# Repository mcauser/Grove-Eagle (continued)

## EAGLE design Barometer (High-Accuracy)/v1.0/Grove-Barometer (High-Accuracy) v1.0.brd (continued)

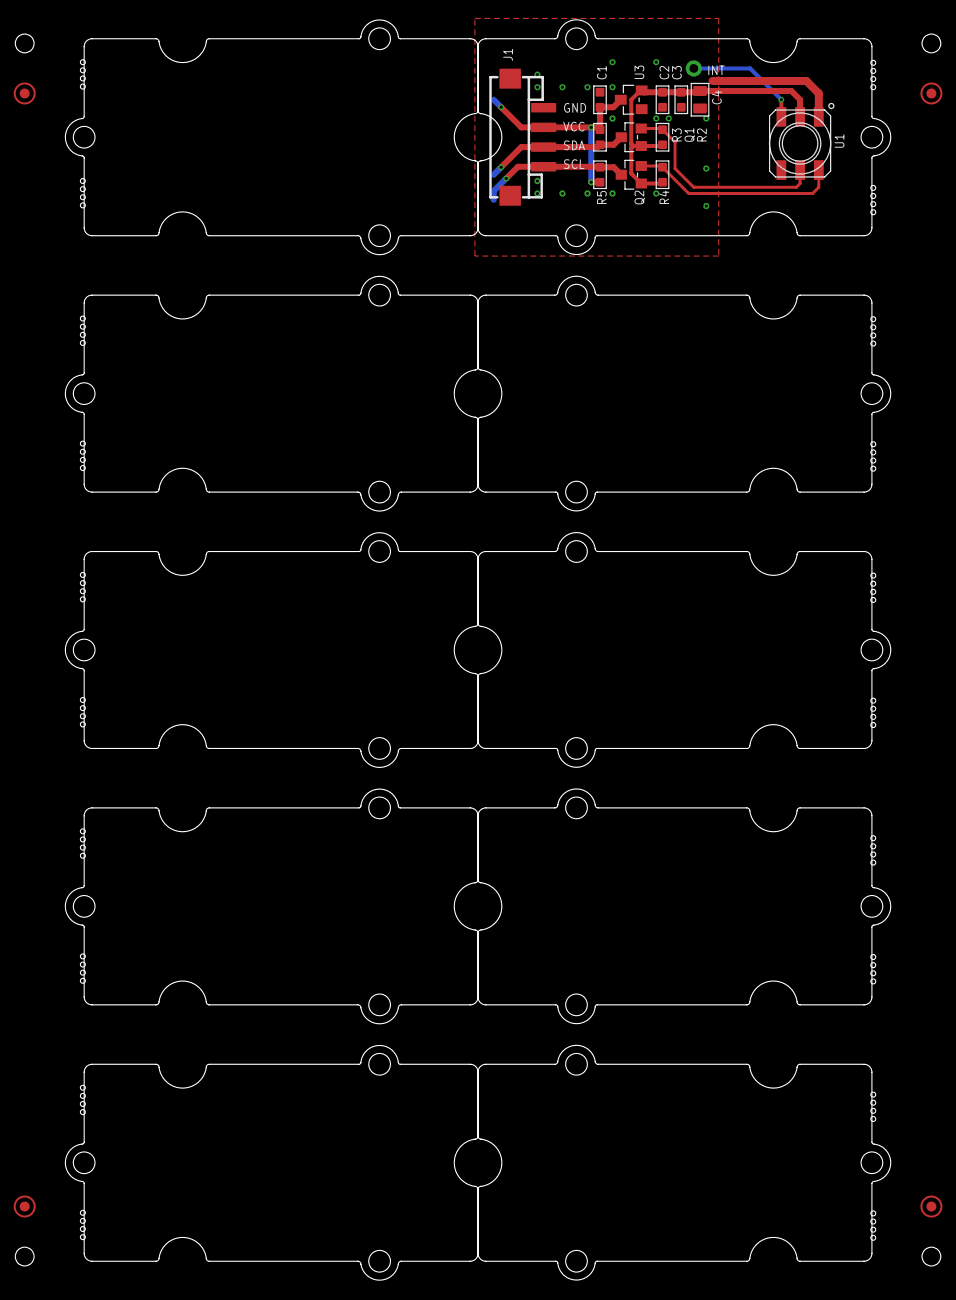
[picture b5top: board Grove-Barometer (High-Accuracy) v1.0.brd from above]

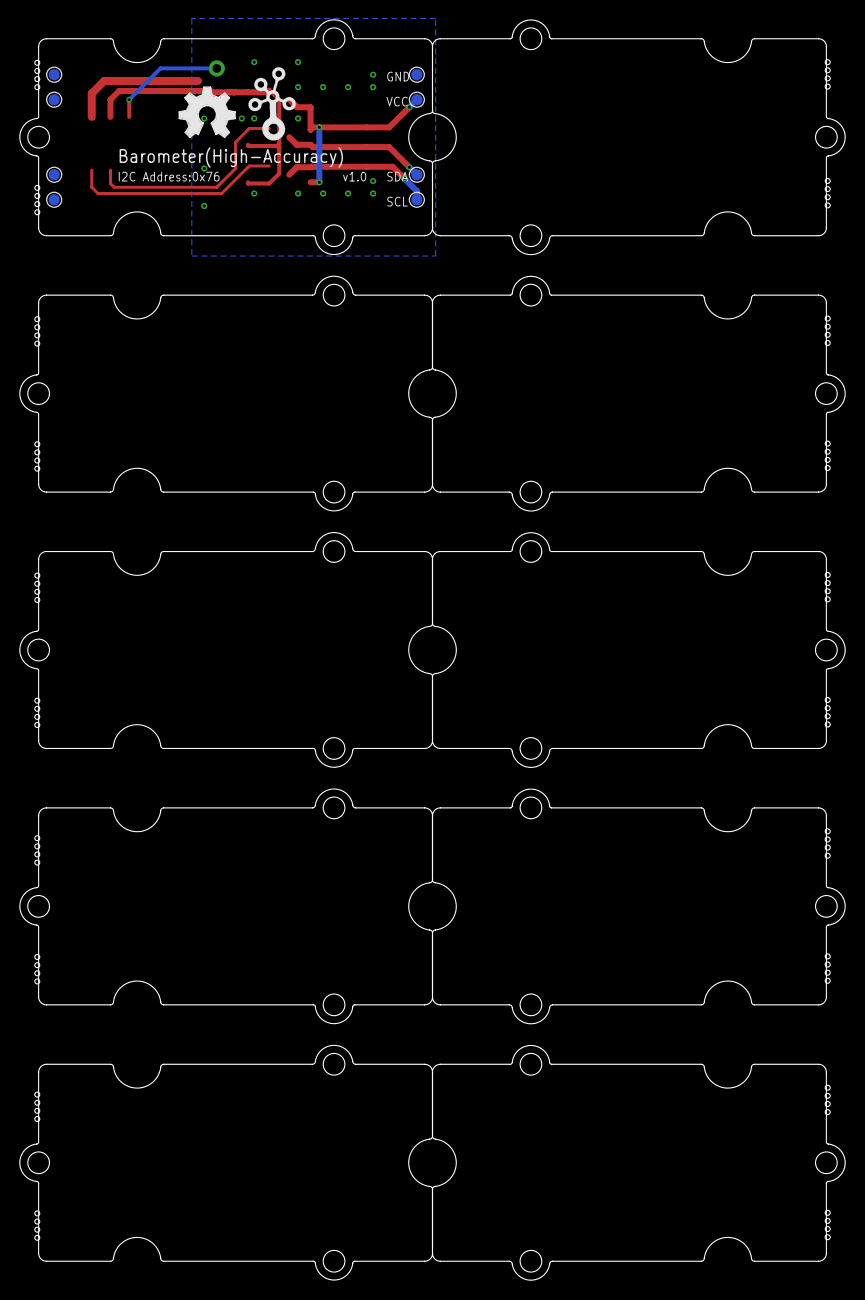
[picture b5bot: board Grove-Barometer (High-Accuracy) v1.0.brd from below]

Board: 2 copper layers, 83.8 x 128.0 mm, 38 parts (10 on the bottom side), 8 nets.

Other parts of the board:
U$4, U$5, U$8, U$9, U$10, U$11, U$12, U$13, U$14, U$15: GROVE-2CONNECTOR-SMD
U$6: OSHW_FILLX200_NOTEXT
U$7: TWIGLOGO

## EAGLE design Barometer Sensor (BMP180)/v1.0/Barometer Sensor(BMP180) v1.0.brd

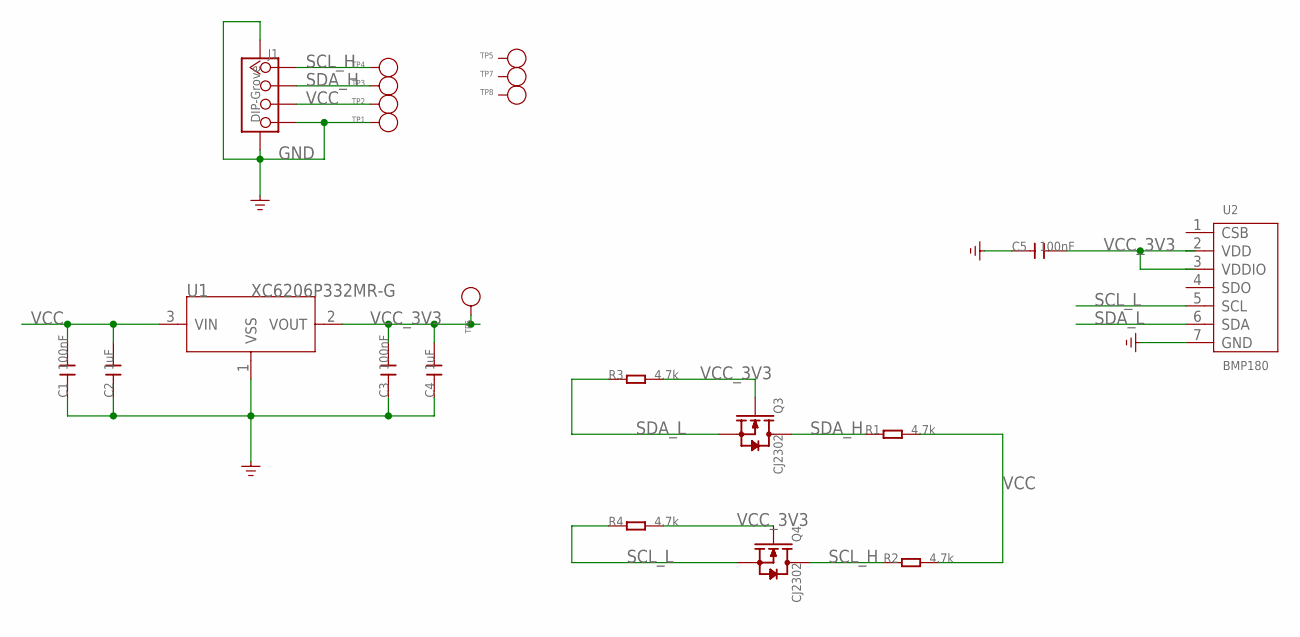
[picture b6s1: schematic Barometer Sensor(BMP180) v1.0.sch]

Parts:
C1, C3, C5: 100nF; C0603
C2, C4: 1uF; C0603
J1: DIP-Grove; 4P-SMD-2.0
Q3, Q4: CJ2302; SOT23
R1, R2, R3, R4: 4.7k; R0603
TP1, TP2, TP3, TP4, TP5, TP6, TP7, TP8: PAD-TEST-POINT'4545'; TP_4545
U1: XC6206P332MR-G; SOT23
U2: BMP180; LGA-7

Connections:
GND: C1.1, C2.1, C3.1, C4.1, J1.4, J1.SS1, J1.SS2, TP1.T, U1.1 (VSS), U2.7 (GND)
SCL_H: J1.1, Q4.3 (D), R2.1, TP4.T
SCL_L: Q4.2 (S), R4.1, U2.5 (SCL)
SDA_H: J1.2, Q3.3 (D), R1.1, TP3.T
SDA_L: Q3.2 (S), R3.1, U2.6 (SDA)
VCC: C1.2, C2.2, J1.3, R1.2, R2.2, TP2.T, U1.3 (VIN)
VCC_3V3: C3.2, C4.2, C5.2, Q3.1 (G), Q4.1 (G), R3.2, R4.2, TP6.T, U1.2 (VOUT), U2.2 (VDD), U2.3 (VDDIO)

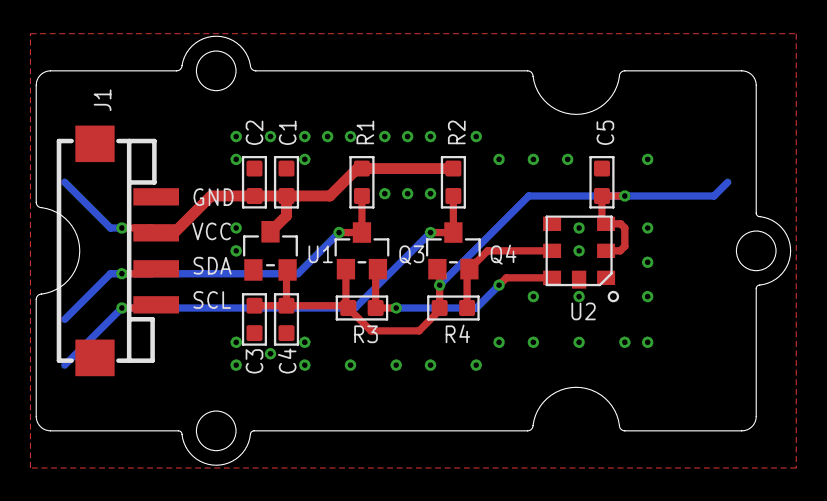
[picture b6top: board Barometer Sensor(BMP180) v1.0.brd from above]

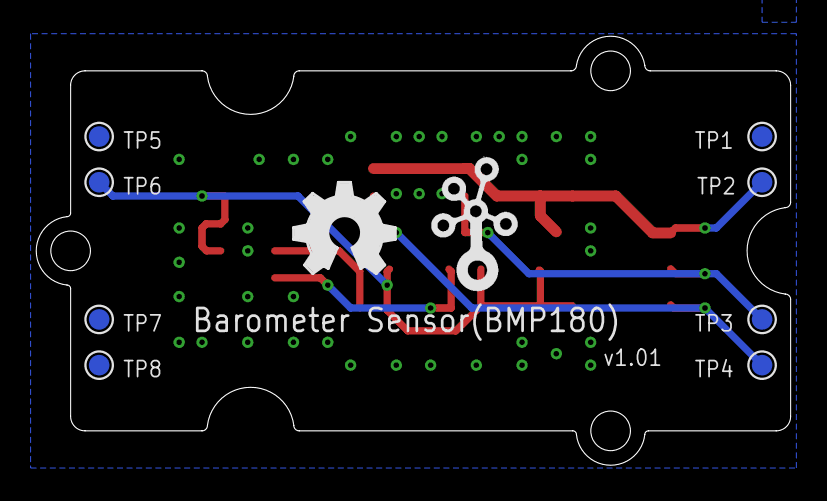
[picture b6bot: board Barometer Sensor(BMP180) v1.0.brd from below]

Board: 2 copper layers, 41.9 x 23.8 mm, 25 parts (10 on the bottom side), 7 nets.

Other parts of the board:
U$6: GROVE-2CONNECTOR-SMD
U$7: OSHW_FILLX200_NOTEXT
U$8: TWIGLOGO
